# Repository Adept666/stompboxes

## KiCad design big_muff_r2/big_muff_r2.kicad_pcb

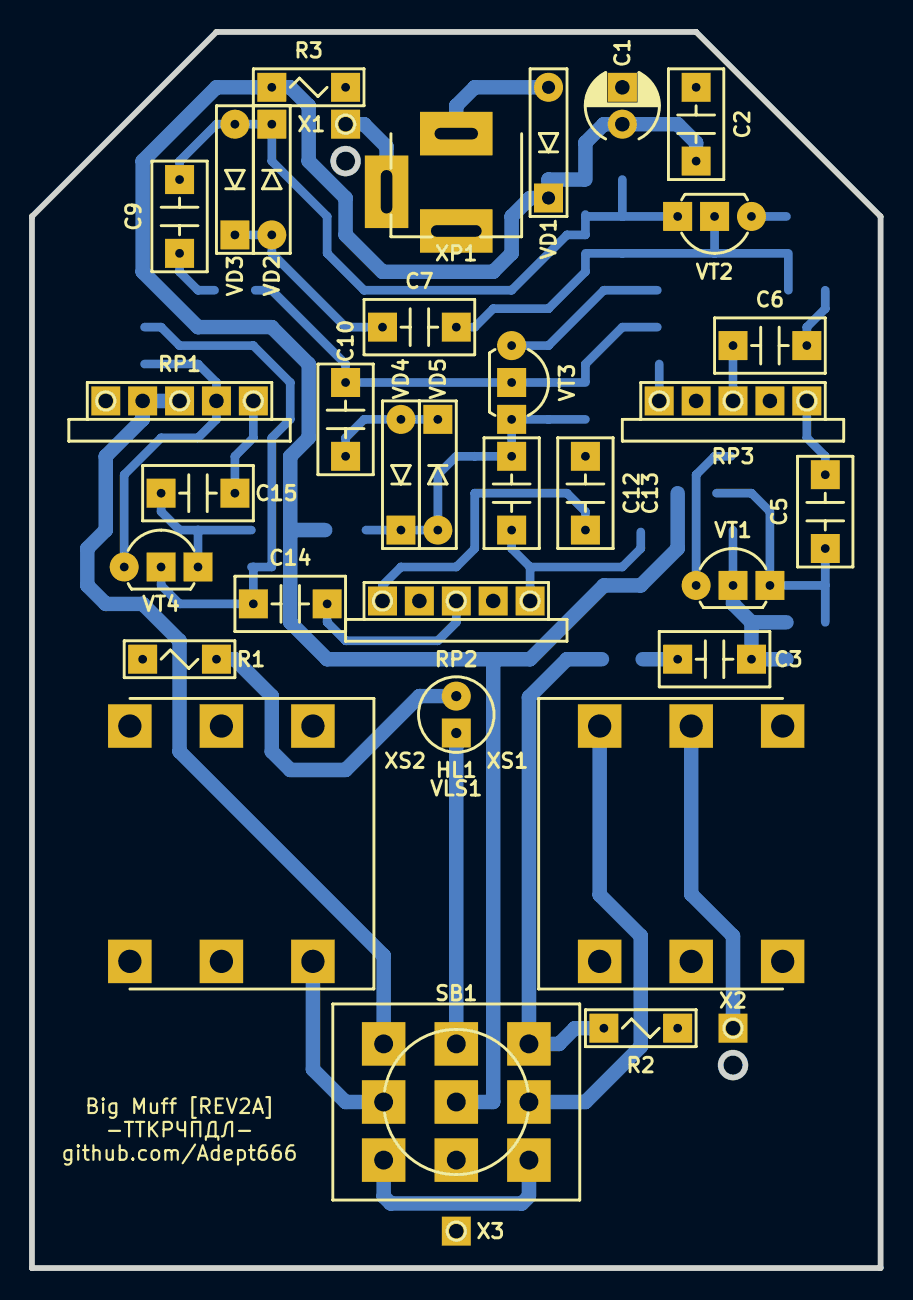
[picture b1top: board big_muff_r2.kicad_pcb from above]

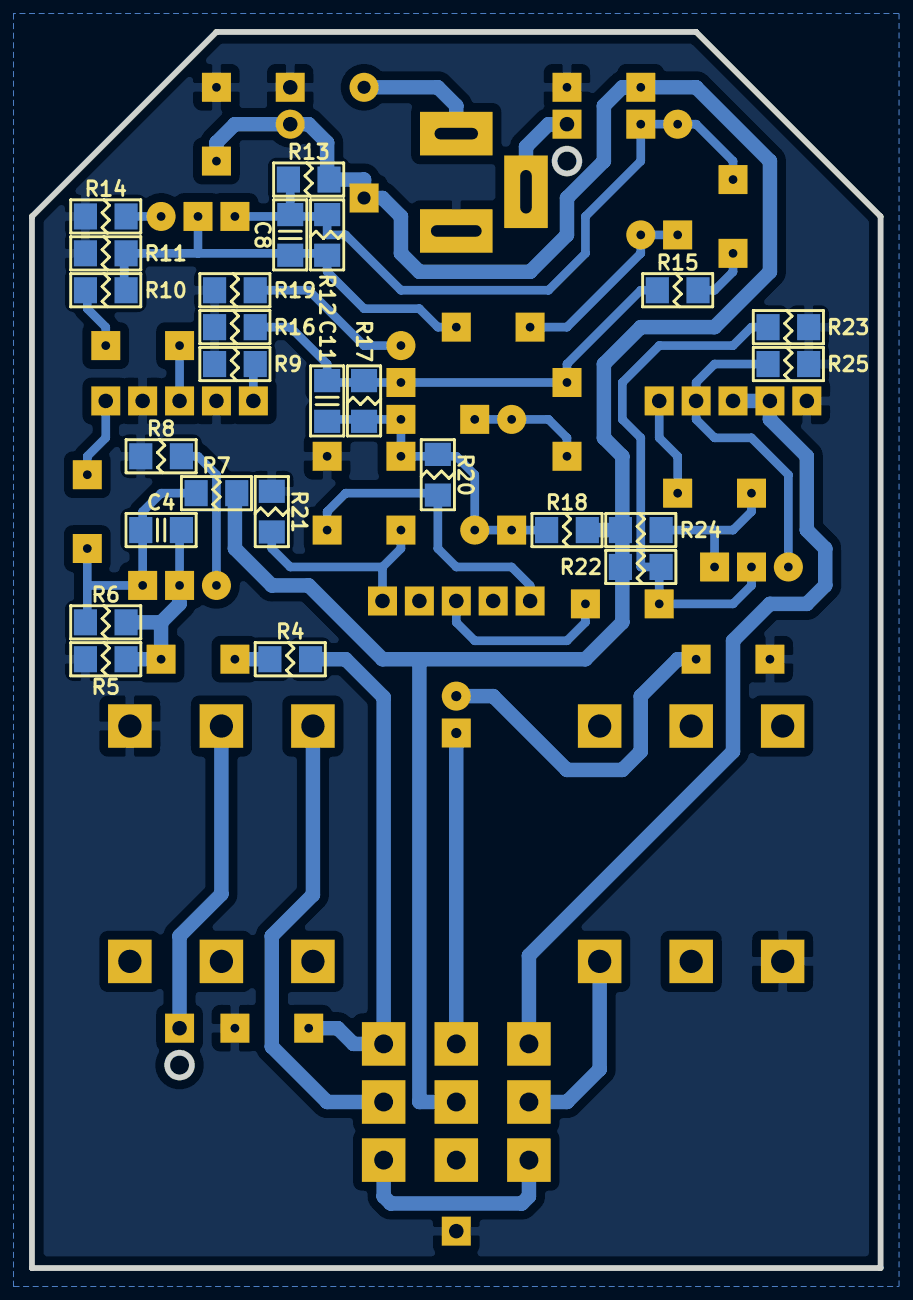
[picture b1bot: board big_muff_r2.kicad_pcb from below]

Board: 2 copper layers, 58.4 x 85.1 mm, 63 parts (25 on the bottom side), 36 nets.

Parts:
C1: 107; CP-RADIAL-D05.0-P02.0-CLS
C2: 104; C-DISK-D04.2-T03.0-P05.08-d0.5
C3, C5, C6, C7, C9, C10, C14, C15: 105; C-DISK-D04.2-T03.0-P05.08-d0.5
C4, C8, C11: 471; C-SM-1206
C12: 392; C-DISK-D04.2-T03.0-P05.08-d0.5
C13: 103; C-DISK-D04.2-T03.0-P05.08-d0.5
GB1: PP3; B-PP3-HV
HL1: FYL-5013UWC; LED-ROUND-05.0-UNI-SH-SPACER
R1: 103; R-MFR-12
R2: 105; R-MFR-12
R3: 223; R-MFR-12
R4: 393; R-SM-1206
R5, R11, R16, R23: 104; R-SM-1206
R6: 514; R-SM-1206
R7, R10, R13, R15, R18, R24: 103; R-SM-1206
R8: 101; R-SM-1206
R9: 182; R-SM-1206
R12, R17, R22: 474; R-SM-1206
R14, R19: 391; R-SM-1206
R20, R21: 223; R-SM-1206
R25: 202; R-SM-1206
RP1, RP3: A100K; RP-PDB181-K-F-PCB-RND
RP2: B100K; RP-PDB181-K-F-PCB-RND
SB1: PBS-24-302SP; SW-PBS-24-302SP
VD1: 5817; P-DO-41
VD2, VD3, VD4, VD5: 6263; P-DO-35
VE1: B013; B013_big_muff_r2a
VLS1: BR-17.8; VLS-BR
VT1, VT2, VT3, VT4: 5088; P-TO-92-E-B-C
X1: +; CON-PAD-S-1.0-2.0
X2: -; CON-PAD-S-1.0-2.0
X3: COM; CON-PAD-S-1.0-2.0
XP1: DC-005S; CON-DC-005S
XS1, XS2: PJ-644C; CON-PJ-644C

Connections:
/IN-CON: SB1.COM3, XS1.T
/IN-SCH: R2.2, R4.1, SB1.NO3
/LED: HL1.A, SB1.NO2
/OUT-CON: SB1.COM1, XS2.T
/OUT-SCH: RP1.2, SB1.NO1
/PP3-NEG: X2.1, XS1.R
/PP3-POS: X1.1, XP1.SN
COM: C1.-, C2.2, C13.2, R1.1, R2.1, R3.1, R5.1, R8.1, R9.1, R11.1, R14.1, R16.1, R19.1, R21.2, R23.1, R25.1, RP1.1, X3.1, XP1.C, XS1.S, XS2.S
unnamed: C3.1, R4.2
unnamed: C3.2, C4.1, R5.2, R6.1, VT1.B
unnamed: C4.2, C5.1, R6.2, R7.1, VT1.C
unnamed: C5.2, RP3.3
unnamed: C6.1, RP3.2
unnamed: C6.2, R10.1
unnamed: C7.1, C8.1, R10.2, R11.2, R12.1, VT2.B
unnamed: C7.2, VD2.A, VD3.C
unnamed: C8.2, C9.1, R12.2, R13.1, VD2.C, VD3.A, VT2.C
unnamed: C9.2, R15.1
unnamed: C10.1, C11.1, R15.2, R16.2, R17.1, VT3.B
unnamed: C10.2, VD4.A, VD5.C
unnamed: C11.2, C12.1, R17.2, R18.1, R20.1, VD4.C, VD5.A, VT3.C
unnamed: C12.2, R21.1, RP2.3
unnamed: C13.1, R20.2, RP2.1
unnamed: C14.1, RP2.2
unnamed: C14.2, R22.1, R23.2, VT4.B
unnamed: C15.1, R24.1, VT4.C
unnamed: C15.2, RP1.3
unnamed: HL1.C, R1.2
unnamed: R8.2, VT1.E
unnamed: R9.2, RP3.1
unnamed: R14.2, VT2.E
unnamed: R19.2, VT3.E
unnamed: R25.2, VT4.E
unnamed: SB1.NC1, SB1.NC3
unnamed: VD1.A, XP1.S
V: C1.+, C2.1, R3.2, R7.2, R13.2, R18.2, R22.2, R24.2, SB1.COM2, VD1.C

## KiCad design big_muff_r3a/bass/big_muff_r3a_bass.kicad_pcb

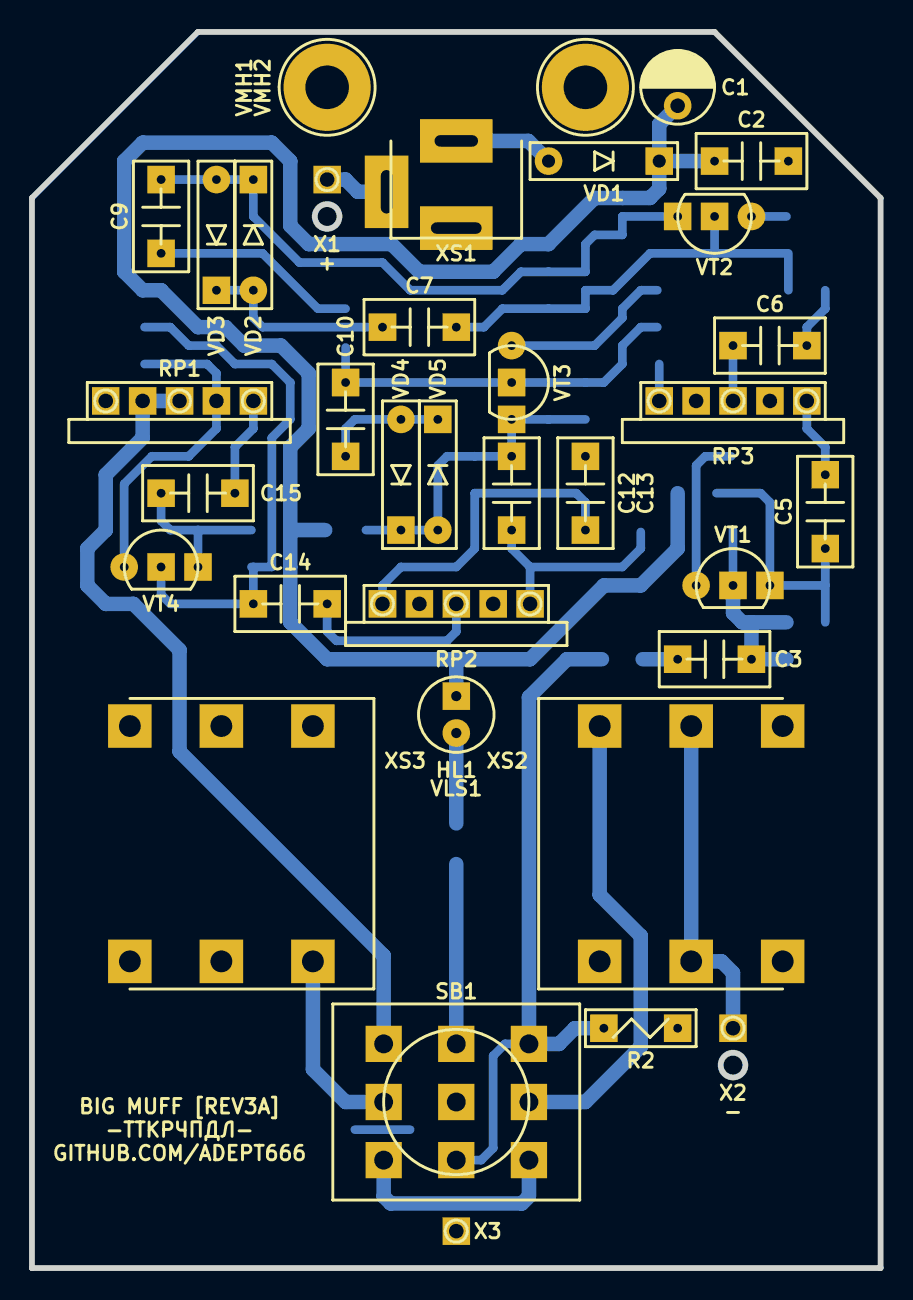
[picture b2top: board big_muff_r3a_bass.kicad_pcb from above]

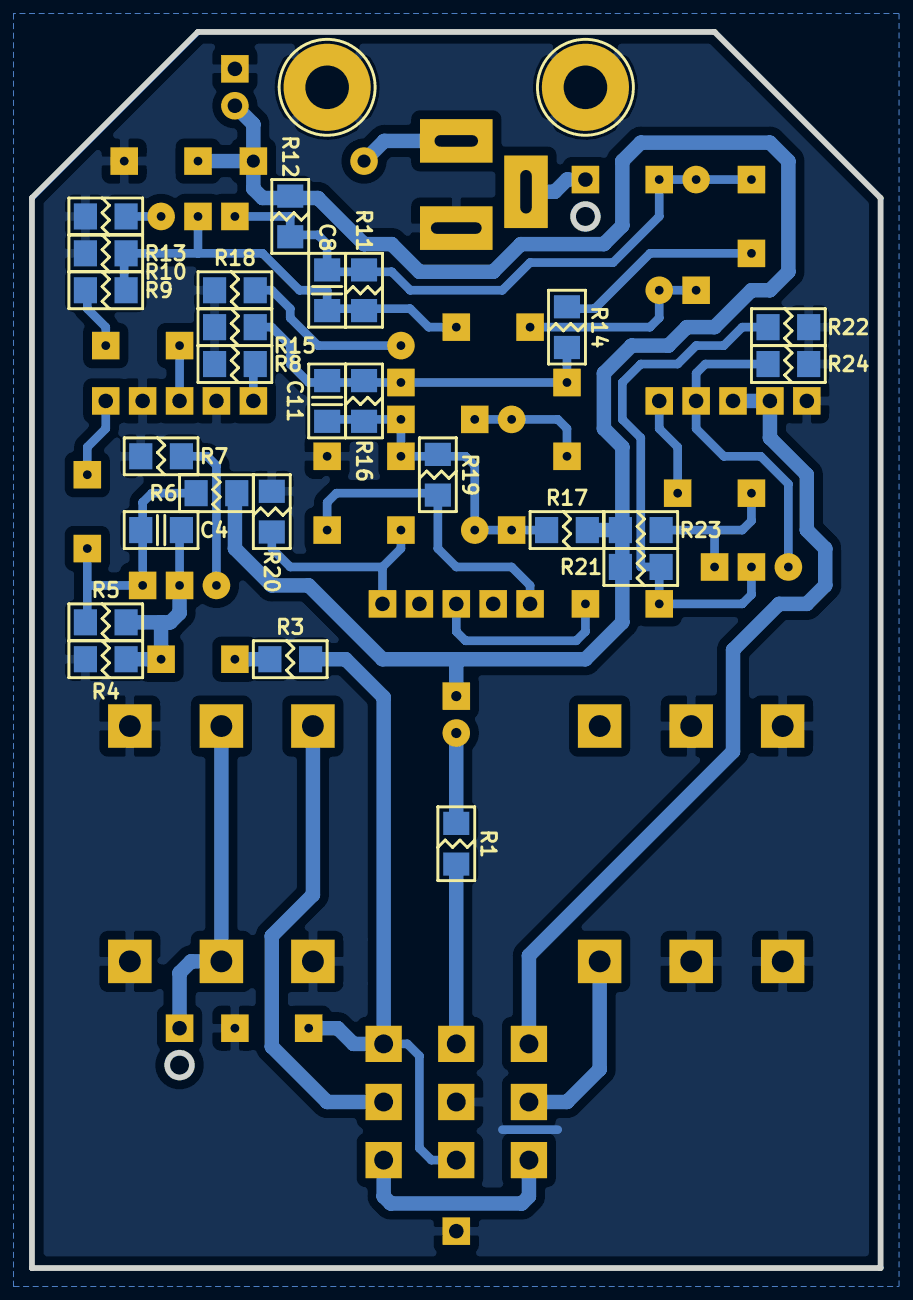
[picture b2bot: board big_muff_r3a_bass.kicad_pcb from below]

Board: 2 copper layers, 58.4 x 85.1 mm, 64 parts (26 on the bottom side), 36 nets.

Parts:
C1: 106; CP-RADIAL-D05.0-P02.0-CLS
C2, C5, C6, C9, C15: 104; C-DISK-D04.2-T03.0-P05.08-d0.5
C3, C14: 105; C-DISK-D04.2-T03.0-P05.08-d0.5
C4, C8, C11: 471; C-SM-1206
C7, C10: 683; C-DISK-D04.2-T03.0-P05.08-d0.5
C12: 332; C-DISK-D04.2-T03.0-P05.08-d0.5
C13: 103; C-DISK-D04.2-T03.0-P05.08-d0.5
GB1: PP3; B-PP3-HV
HL1: FYL-5013UWC; LED-ROUND-05.0-UNI-SH-SPACER-PNL-5.3
R1, R9, R14, R23: 103; R-SM-1206
R2: 105; R-MFR-12
R3: 393; R-SM-1206
R4, R10, R15, R22: 104; R-SM-1206
R5, R11, R16, R21: 474; R-SM-1206
R6, R12, R17: 123; R-SM-1206
R7, R13, R18: 391; R-SM-1206
R8: 102; R-SM-1206
R19, R20: 223; R-SM-1206
R24: 272; R-SM-1206
RP1, RP3: A100K; RPB-18-1x17-1.6-PNL-7.4-2.8
RP2: B100K; RPB-18-1x17-1.6-PNL-7.4-2.8
SB1: PBS-24-302SP; SW-PBS-24-302SP-2.5-PNL-13.0
VD1: 5817; P-DO-41
VD2, VD3, VD4, VD5: 4148; P-DO-35
VE1: B013; B013_E1
VLS1: BR-12.7; VLS-BR
VMH1, VMH2: DI5M3x18; VMH-STA-DA5-PNL-3.0
VT1, VT2, VT3, VT4: 547; P-TO-92-E-B-C
X1: +; CON-PAD-S-1.0-1.9
X2: -; CON-PAD-S-1.0-1.9
X3: COM; CON-PAD-S-1.0-1.9
XS1: DC-005; CON-DC-005
XS2, XS3: PJ-644C; CON-PJ-644C

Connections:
/IN-CIR: R2.2, R3.1, SB1.NC2, SB1.NO3
/IN-CON: SB1.COM3, XS2.T
/LED: R1.1, SB1.NO2
/OUT-CIR: RP1.2, RP1.NC1, SB1.NO1
/OUT-CON: SB1.COM1, XS3.T
/PP3-NEG: X2.1, XS2.R, XS2.RN
/PP3-POS: X1.1, XS1.SN
COM: C1.-, C2.2, C13.2, R2.1, R4.1, R7.1, R8.1, R10.1, R13.1, R15.1, R18.1, R20.2, R22.1, R24.1, RP1.1, RP3.NC1, RP3.NC2, SB1.COM2, VMH1.0, VMH2.0, X3.1, XS1.C, XS2.S, XS2.SN, XS2.TN, XS3.R, XS3.RN, XS3.S, XS3.SN
unnamed: C3.1, R3.2
unnamed: C3.2, C4.1, R4.2, R5.1, VT1.B
unnamed: C4.2, C5.1, R5.2, R6.1, VT1.C
unnamed: C5.2, RP3.3
unnamed: C6.1, RP3.2
unnamed: C6.2, R9.1
unnamed: C7.1, C8.1, R9.2, R10.2, R11.1, VT2.B
unnamed: C7.2, VD2.A, VD3.C
unnamed: C8.2, C9.1, R11.2, R12.1, VD2.C, VD3.A, VT2.C
unnamed: C9.2, R14.1
unnamed: C10.1, C11.1, R14.2, R15.2, R16.1, VT3.B
unnamed: C10.2, VD4.A, VD5.C
unnamed: C11.2, C12.1, R16.2, R17.1, R19.1, VD4.C, VD5.A, VT3.C
unnamed: C12.2, R20.1, RP2.3
unnamed: C13.1, R19.2, RP2.1
unnamed: C14.1, RP2.2
unnamed: C14.2, R21.1, R22.2, VT4.B
unnamed: C15.1, R23.1, VT4.C
unnamed: C15.2, RP1.3
unnamed: HL1.C, R1.2
unnamed: R7.2, VT1.E
unnamed: R8.2, RP3.1
unnamed: R13.2, VT2.E
unnamed: R18.2, VT3.E
unnamed: R24.2, RP1.NC2, VT4.E
unnamed: SB1.NC1, SB1.NC3
unnamed: VD1.A, XS1.S
V: C1.+, C2.1, HL1.A, R6.2, R12.2, R17.2, R21.2, R23.2, VD1.C

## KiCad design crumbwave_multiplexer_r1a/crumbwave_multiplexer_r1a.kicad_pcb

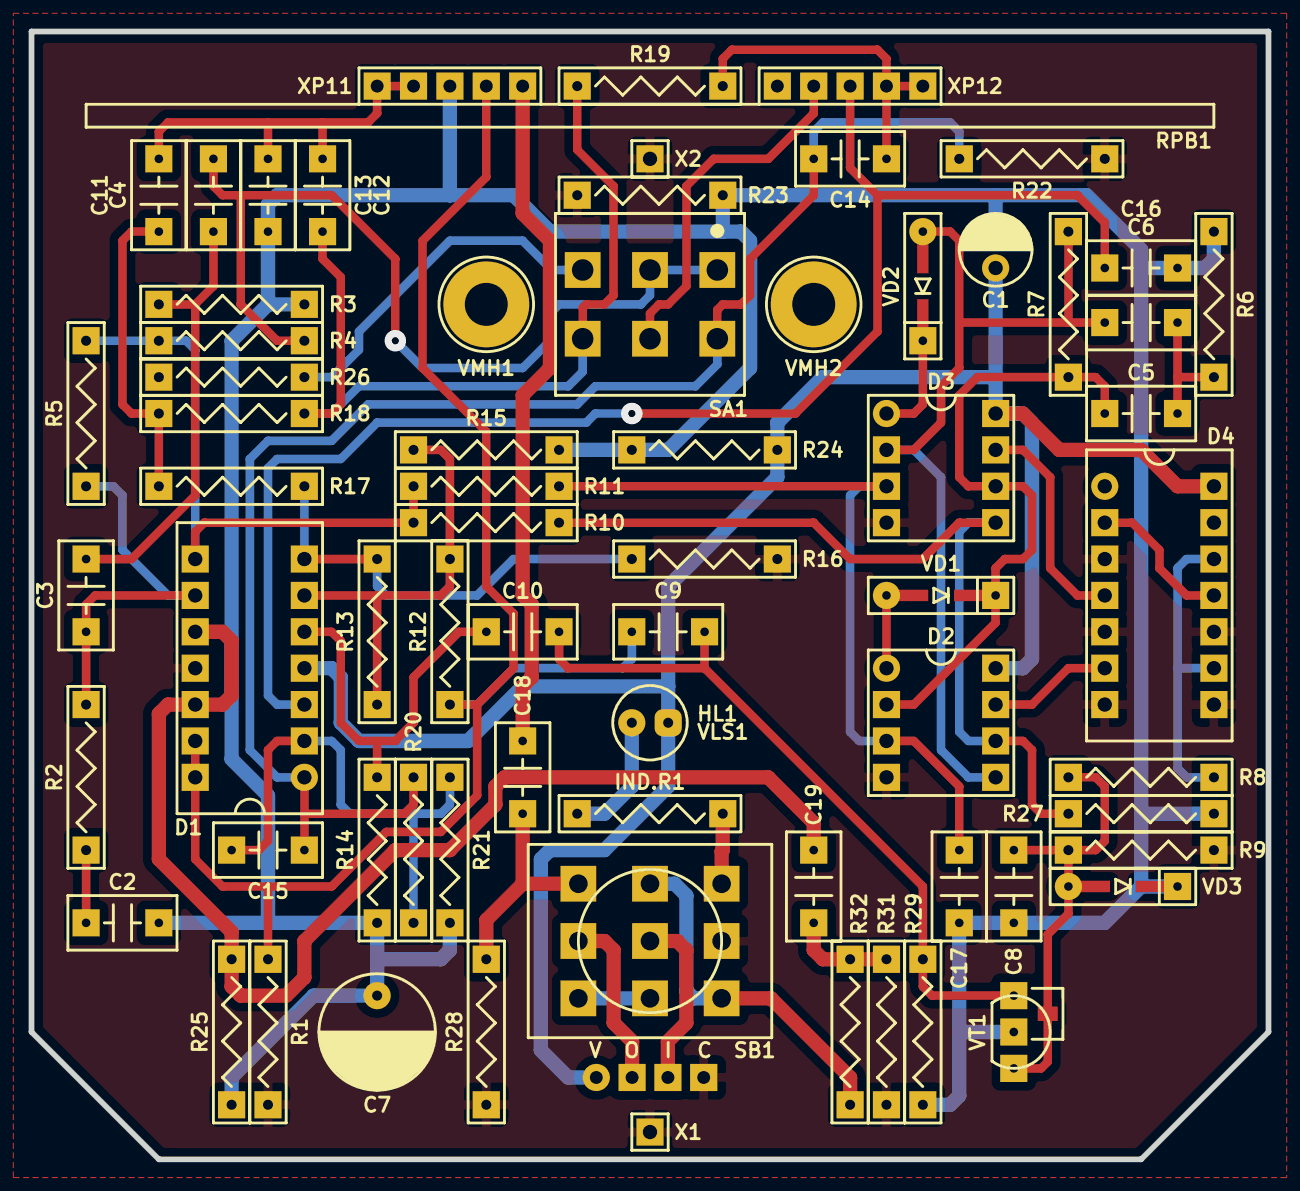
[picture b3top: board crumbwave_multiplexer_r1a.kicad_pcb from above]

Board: 2 copper layers, 86.4 x 78.7 mm, 71 parts (1 on the bottom side), 44 nets.

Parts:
C1: 336; CP-RADIAL-D05.0-P02.0-CLS
C2, C5, C6, C9, C10, C18, C19: 104; C-DISK-D04.2-T03.0-P05.08-d0.5
C3, C4, C8, C13, C15, C16, C17: 223; C-DISK-D04.2-T03.0-P05.08-d0.5
C7: 477; CP-RADIAL-D08.0-P03.5-d0.6
C11, C12: 154; C-DISK-D04.2-T03.0-P05.08-d0.5
C14: 473; C-DISK-D04.2-T03.0-P05.08-d0.5
D1: 324; P-DIP-14
D2, D3: 4558; P-DIP-08
D4: 4013; P-DIP-14
HL1: FYL-5013URC; LED-ROUND-05.0-UNI-SH-SPACER-PNL-5.3
IND.R1: 472; R-MFR-25
R1, R10, R11, R12, R16, R22: 103; R-MFR-25
R2, R14, R25, R27: 104; R-MFR-25
R3, R19: 183; R-MFR-25
R4, R13, R23, R24: 153; R-MFR-25
R5: 334; R-MFR-25
R6: 471; R-MFR-25
R7: 184; R-MFR-25
R8, R9, R15: 273; R-MFR-25
R17, R18: 472; R-MFR-25
R20, R21: 473; R-MFR-25
R26: 681; R-MFR-25
R28, R31: 225; R-MFR-25
R29: 154; R-MFR-25
R32: 102; R-MFR-25
RPB1: A100K-B100K-B100K; RPB-1590BB2-18-3x17-1.6-PNL-7.4-2.8
SA1: MTS-202-A2; SW-MTS-202-A2-2.5-PNL-6.0
SB1: PBS-24-302SP; SW-PBS-24-302SP-2.5-PNL-13.0
VD1, VD2, VD3: 4148; P-SOD-123-OR-DO-35-V1
VE1: 1590BB2; 1590BB2_A1
VLS1: BR-12.7; VLS-BR
VMH1, VMH2: DI5M3x18; VMH-STA-DA5-PNL-3.0
VT1: 5457; P-SOT-23-D-S-G-OR-TO-92-D-S-G
X1, X2: COM; CON-PAD-S-1.0-1.9
XB1: 1590BB2 Connector Board Extended; XB-1590BB2-EXTENDED
XP1: B4B-XH-A; CON-XH-B4B-A

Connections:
/BF-IN: C12.1, R18.2, R19.1, SA1.NO2
/BF-OUT: C14.1, C15.1, D1.1, R20.2, R22.2, SA1.NC2
/DRY: C9.1, D1.13, D1.14, R1.2, R12.1, RPB1.21
/IN-CIR: R32.1, SB1.NC3, SB1.NO2
/IN-CON: SB1.COM2, XP1.3
/LED: IND.R1.1, SB1.NO3
/OUT-CIR: C18.2, R28.2, SB1.NO1
/OUT-CON: SB1.COM1, XP1.2
/RANGE: C4.2, R4.1, SA1.COM1, SA1.NC1
/RANGE-HIGH: R26.2, SA1.NO1
/RESET: D3.7, D4.4
/SET: D2.7, D4.6
/WET: RPB1.23, SA1.COM2
COM: C7.-, D1.11, D2.4, D3.4, D4.3, D4.5, D4.7, D4.8, D4.10, R1.1, R9.1, R16.1, R22.1, R23.1, R26.1, R28.1, R31.1, SB1.COM3, X1.1, X2.1, XP1.4
unnamed: C2.1, R2.1
unnamed: C3.1, D1.9, R2.2, R5.1
unnamed: C3.2, C4.1, R3.2
unnamed: C5.1, D2.2, D3.6, R7.2, VD1.C
unnamed: C5.2, C6.1, R6.2
unnamed: C6.2, D2.5, D3.2, R7.1, VD2.A
unnamed: C8.1, R8.1, R9.2, VD3.A, VT1.G
unnamed: C9.2, C10.1, R29.2, VT1.D
unnamed: C10.2, D1.5, R14.2
unnamed: C11.1, R17.2, R18.1
unnamed: C11.2, C12.2, C13.1, RPB1.12, RPB1.13
unnamed: C14.2, R19.2, RPB1.31, RPB1.32
unnamed: C15.2, D1.2, R20.1, R21.2
unnamed: C16.1, D1.3, RPB1.33
unnamed: C17.1, D2.3, D3.3, R11.1
unnamed: C18.1, RPB1.22
unnamed: C19.1, R31.2, R32.2
unnamed: C19.2, D1.10, D1.12, R25.2
unnamed: D1.6, R12.2, R13.1, R15.2
unnamed: D1.7, R13.2, R16.2, R17.1
unnamed: D1.8, R4.2, R5.2, R10.2, R11.2
unnamed: D2.1, VD1.A
unnamed: D2.6, D3.5, R10.1, R27.2
unnamed: D3.1, VD2.C
unnamed: D4.2, D4.11
unnamed: D4.9, D4.12, R8.2
unnamed: HL1.C, IND.R1.2
unnamed: SB1.NC1, SB1.NC2
V: C1.+, D1.4, D2.8, D3.8, D4.14, HL1.A, R24.2, XP1.1
VREF: C1.-, C2.2, C7.+, C8.2, C13.2, C16.2, C17.2, R3.1, R6.1, R14.1, R15.1, R21.1, R23.2, R24.1, R25.1, R27.1, R29.1, RPB1.11, VD3.C, VT1.S

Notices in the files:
big_muff_r2/big_muff_r2.kicad_pcb:
This project is licensed under GNU General Public License v3.0 or later
